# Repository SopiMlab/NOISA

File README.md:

NOISA, Network of Intelligent Sonic Agents, offers a solution for enhancing the quality of performer’s engagement in musical interaction. NOISA project provides an intelligent system that acts to maintain and deepen the performers en- gagement by learning from the performer’s actions and behavioural patterns while playing NOISA instruments. It monitors the internal states of a performer ( e.g. motivation, affective states and reactiveness) and acts to maintain these states; if the performer loses individual motivation or interest, the system reacts by changing its physical control-behaviour of the interface in order to make the interaction interesting again.

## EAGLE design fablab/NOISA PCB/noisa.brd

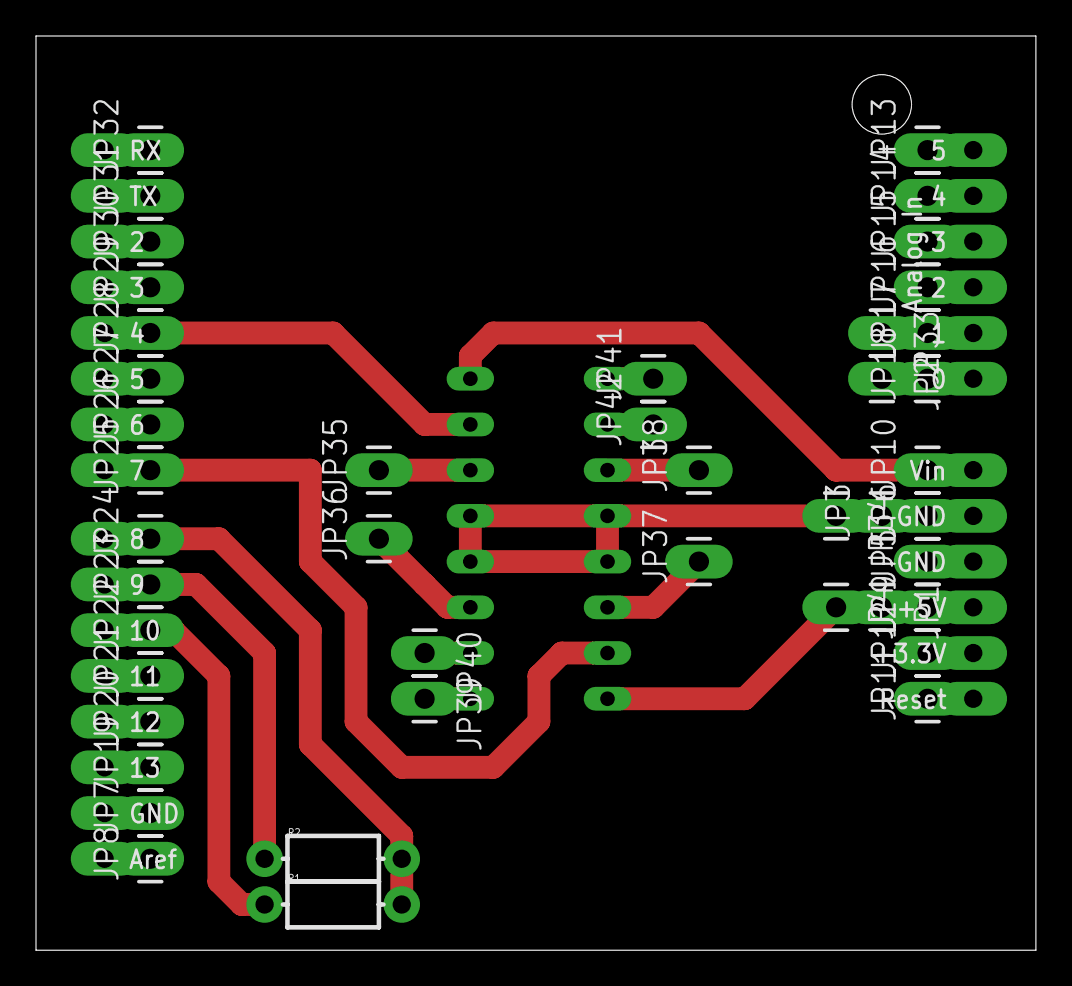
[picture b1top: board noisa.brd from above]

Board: 2 copper layers, 55.5 x 50.8 mm, 46 parts (1 on the bottom side), 31 nets.

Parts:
IC1: L293D; DIL16
JP1, JP2, JP3, JP4, JP5, JP6, JP7, JP8, JP9, JP10, JP11, JP12, JP13, JP14, JP15, JP16, JP17, JP18, JP19, JP20, JP21, JP22, JP23, JP24, JP25, JP26, JP27, JP28, JP29, JP30, JP31, JP32, JP33, JP34, JP35, JP36, JP37, JP38, JP39, JP40, JP41, JP42: M01PTH_LONGPAD; 1X01_LONGPAD
R1, R2: AXIAL-0.3-KIT
U1: ARDUINO_SHIELDLONGPADS; DUEMILANOVE_SHIELD_LONGPADS

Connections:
unnamed: JP5.1, U1.GND@0
unnamed: IC1.8, JP10.1, U1.VIN
unnamed: IC1.16, JP1.1, JP4.1, JP9.1, U1.5V
unnamed: IC1.1, JP29.1, JP39.1, U1.D3
unnamed: IC1.7, JP28.1, U1.D4
unnamed: IC1.2, JP30.1, JP40.1, U1.D2
unnamed: IC1.9, JP26.1, JP41.1, U1.D6
unnamed: IC1.10, JP27.1, JP42.1, U1.D5
unnamed: IC1.15, JP25.1, U1.D7
unnamed: IC1.3, JP36.1
unnamed: IC1.6, JP35.1
unnamed: IC1.14, JP37.1
unnamed: IC1.11, JP38.1
unnamed: JP2.1, JP18.1, U1.A0
unnamed: JP17.1, JP33.1, U1.A1
unnamed: IC1.4, IC1.5, IC1.12, IC1.13, JP3.1, JP6.1, JP34.1, U1.GND@1
unnamed: JP7.1, U1.GND@2
unnamed: JP8.1, U1.AREF
unnamed: JP11.1, U1.RES
unnamed: JP13.1, U1.A5
unnamed: JP14.1, U1.A4
unnamed: JP15.1, U1.A3
unnamed: JP16.1, U1.A2
unnamed: JP19.1, U1.D13
unnamed: JP20.1, U1.D12
unnamed: JP21.1, U1.D11
unnamed: JP22.1, R1.P$1, U1.D10
unnamed: JP23.1, R2.P$1, U1.D9
unnamed: JP24.1, R1.P$2, R2.P$2, U1.D8
unnamed: JP31.1, U1.TX
unnamed: JP32.1, U1.RX

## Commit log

2015-05-26 Tue 26 May 2015
2015-05-26 NOISA Instruments lasercut/print documents
2015-05-26 motorised sliders/capasity sensors Arduino documents
2015-05-26 NOISA Instrument agent 2 sound synthesis Pd patches
2015-05-26 NOISA Instrument agent 1 sound synthesis Pd patches
2015-05-26 NOISA Instrument agent 3 sound synthesis Pd patches
2015-05-26 MYO EMG data extraction / modiefied from MYO SDK
2015-05-26 NOISA system components including Engagement Prediction Module, Gesture Analysis Module, System Response Module
2015-05-26 MYO EMG data extraction / modified from MYO SDK
2015-06-15 updateJune

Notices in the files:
parts and their libraries:
SparkFun-Connectors: Licensing: Creative Commons ShareAlike 4.0 International - https://creativecommons.org/licenses/by-sa/4.0
